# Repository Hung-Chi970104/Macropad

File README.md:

# From Zero to Macropad
This is my first time designing a PCB and 3D modeling using fusion 360.
My goal is to build a macropad with 9 keys, and I will be making it a numpad first. Firmware can always be adjusted to your need.
- Quick glance: https://skfb.ly/pGsA6

## Components
- Arduino Micro Pro
- Cherry MX Key Switches
- 3D printed case

## Design

## Conclusion

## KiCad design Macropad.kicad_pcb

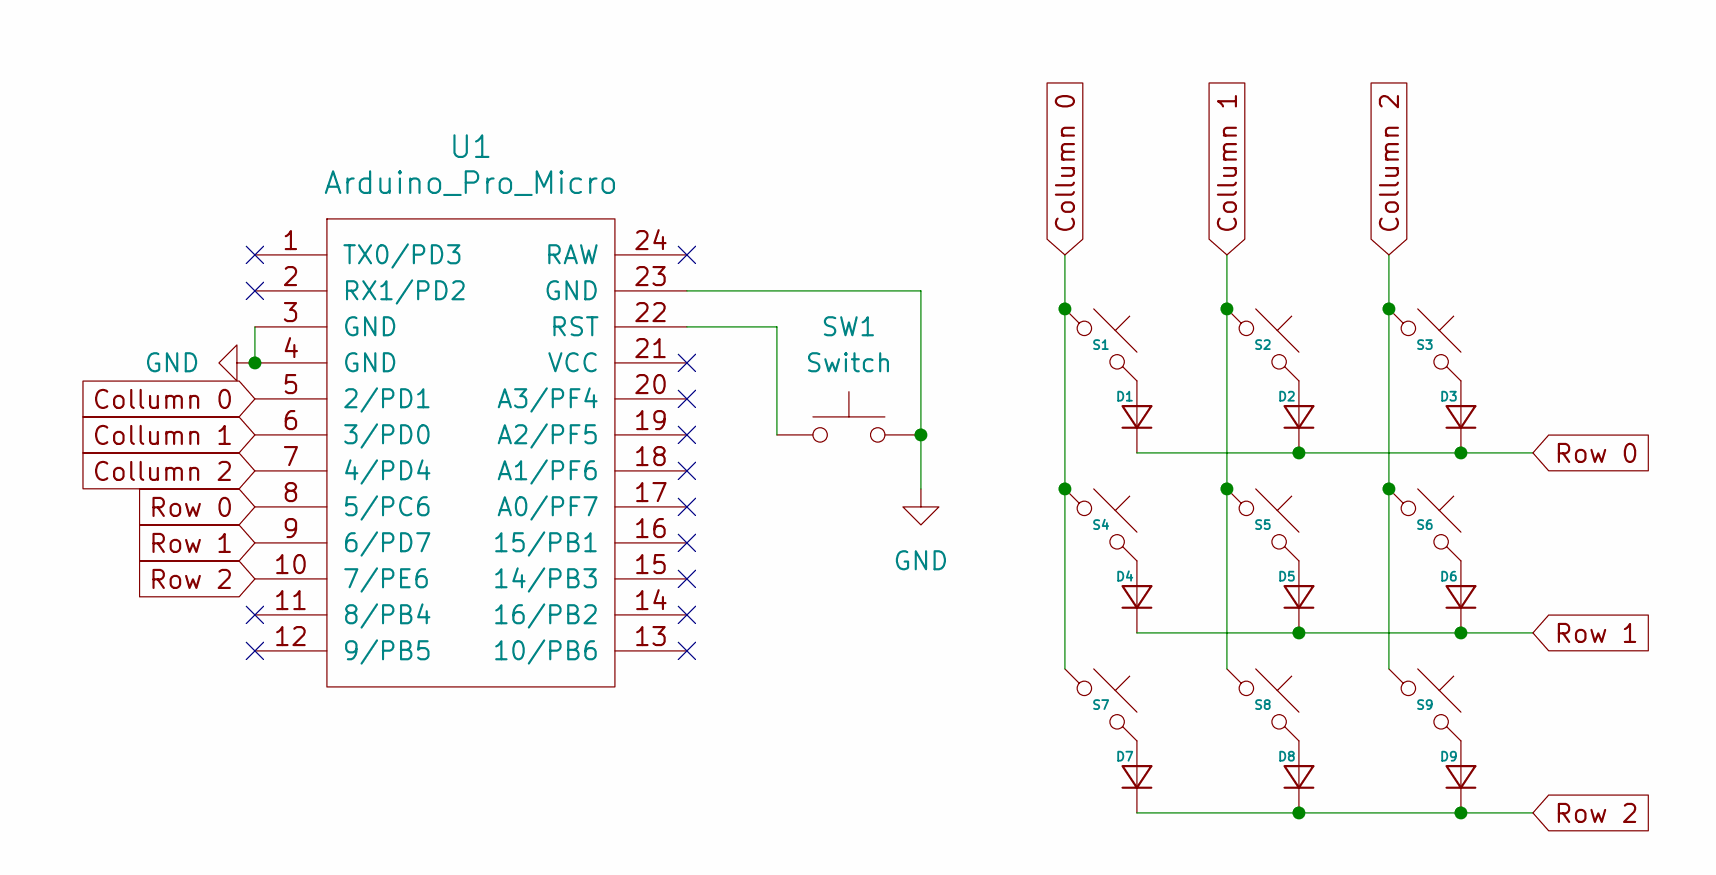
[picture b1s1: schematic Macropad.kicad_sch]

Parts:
D1, D2, D3, D4, D5, D6, D7, D8, D9: Diode_DO-35
S1, S2, S3, S4, S5, S6, S7, S8, S9: MX_PCB_1.00u
SW1: Switch; SW_PUSH_6mm
U1: Arduino_Pro_Micro

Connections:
Collumn 0: S1.1, S4.1, S7.1, U1.5 (2/PD1)
Collumn 1: S2.1, S5.1, S8.1, U1.6 (3/PD0)
Collumn 2: S3.1, S6.1, S9.1, U1.7 (4/PD4)
GND: SW1.2, U1.3 (GND), U1.4 (GND), U1.23 (GND)
unnamed: D1.2 (A), S1.2
unnamed: D2.2 (A), S2.2
unnamed: D3.2 (A), S3.2
unnamed: D4.2 (A), S4.2
unnamed: D5.2 (A), S5.2
unnamed: D6.2 (A), S6.2
unnamed: D7.2 (A), S7.2
unnamed: D8.2 (A), S8.2
unnamed: D9.2 (A), S9.2
unnamed: SW1.1, U1.22 (RST)
Row 0: D1.1 (K), D2.1 (K), D3.1 (K), U1.8 (5/PC6)
Row 1: D4.1 (K), D5.1 (K), D6.1 (K), U1.9 (6/PD7)
Row 2: D7.1 (K), D8.1 (K), D9.1 (K), U1.10 (7/PE6)

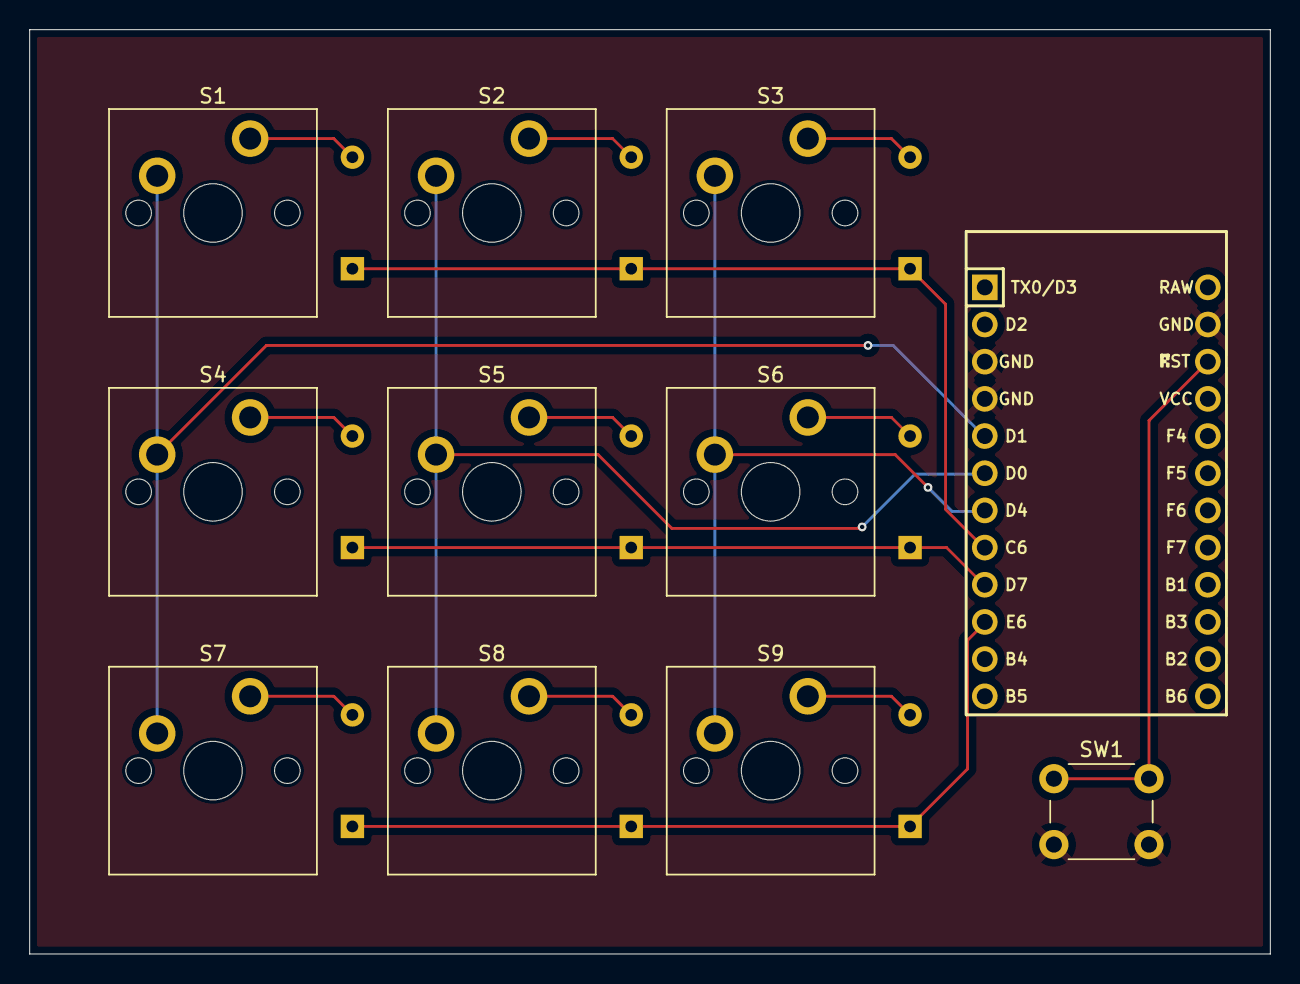
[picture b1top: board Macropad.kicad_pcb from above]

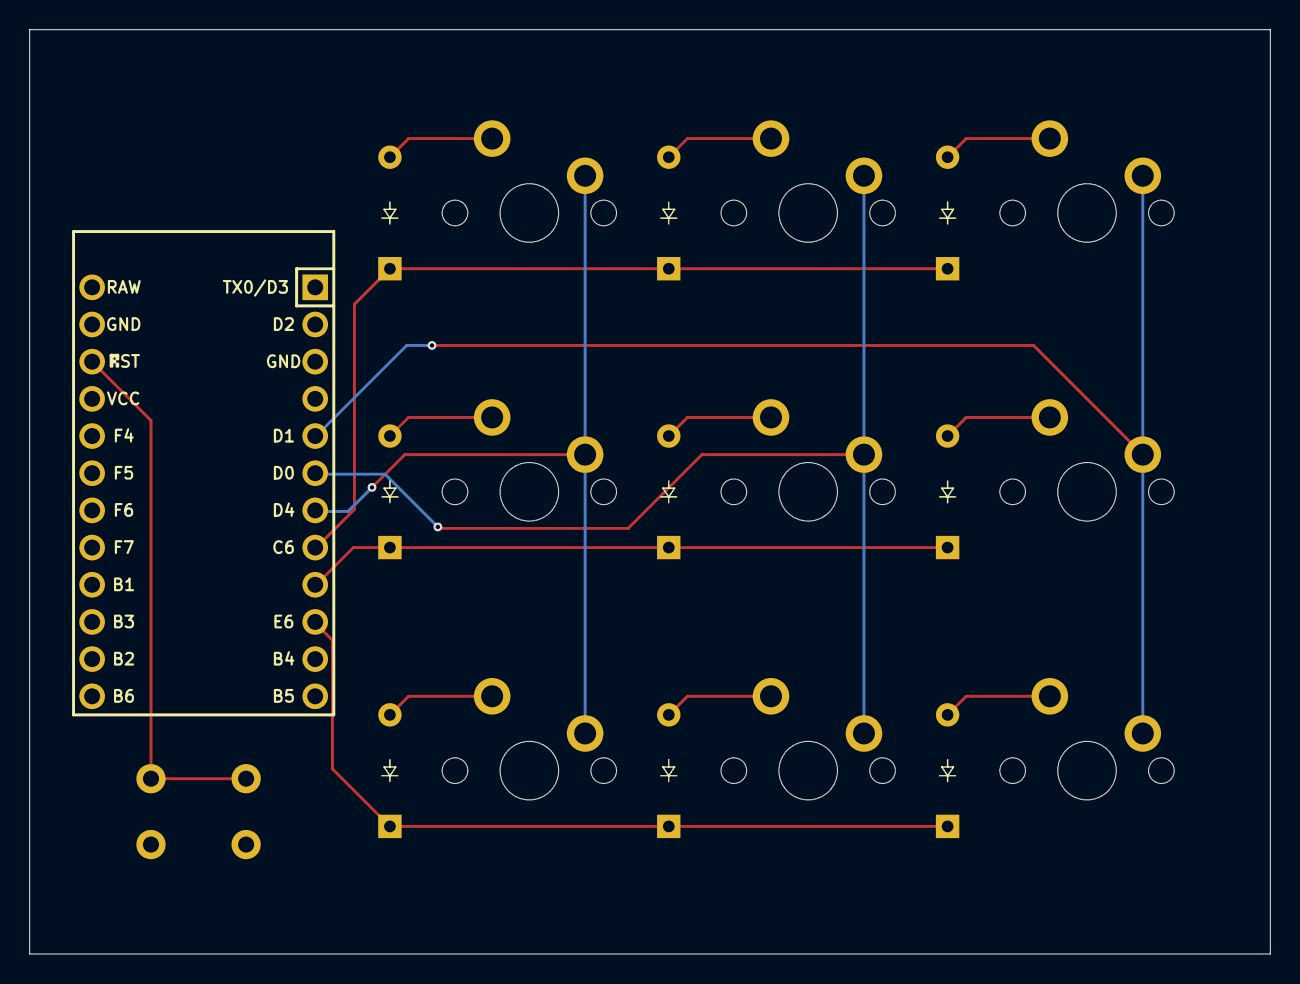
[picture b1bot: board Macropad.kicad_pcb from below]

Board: 2 copper layers, 84.8 x 63.2 mm, 20 parts (9 on the bottom side), 17 nets.

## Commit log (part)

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2025-12-18 Create .gitignore for KiCad project
    Add a .gitignore file for KiCad project files.
2025-12-19 Change PCB dimension + add GND and Reset Button
2025-12-19 Update PCB
2025-12-20 Update schematic
2025-12-20 Add .hex file for firmware
2025-12-20 update latest PCB model
2025-12-20 Export Macropad case
2025-12-22 Add initial README for Macropad project
2025-12-22 Add link to Macropad 3D model
2025-12-22 Fix typo and add image link in README
    Corrected a typo in the README and added an image link.
2025-12-22 Fix image link formatting in README.md
2025-12-22 Update README with more assembled project images
    Added additional images of the assembled project.
2026-02-10 Update README to remove old instructions and add design info
    Removed outdated instructions for viewing the project and added a new design section with quick glance link.
